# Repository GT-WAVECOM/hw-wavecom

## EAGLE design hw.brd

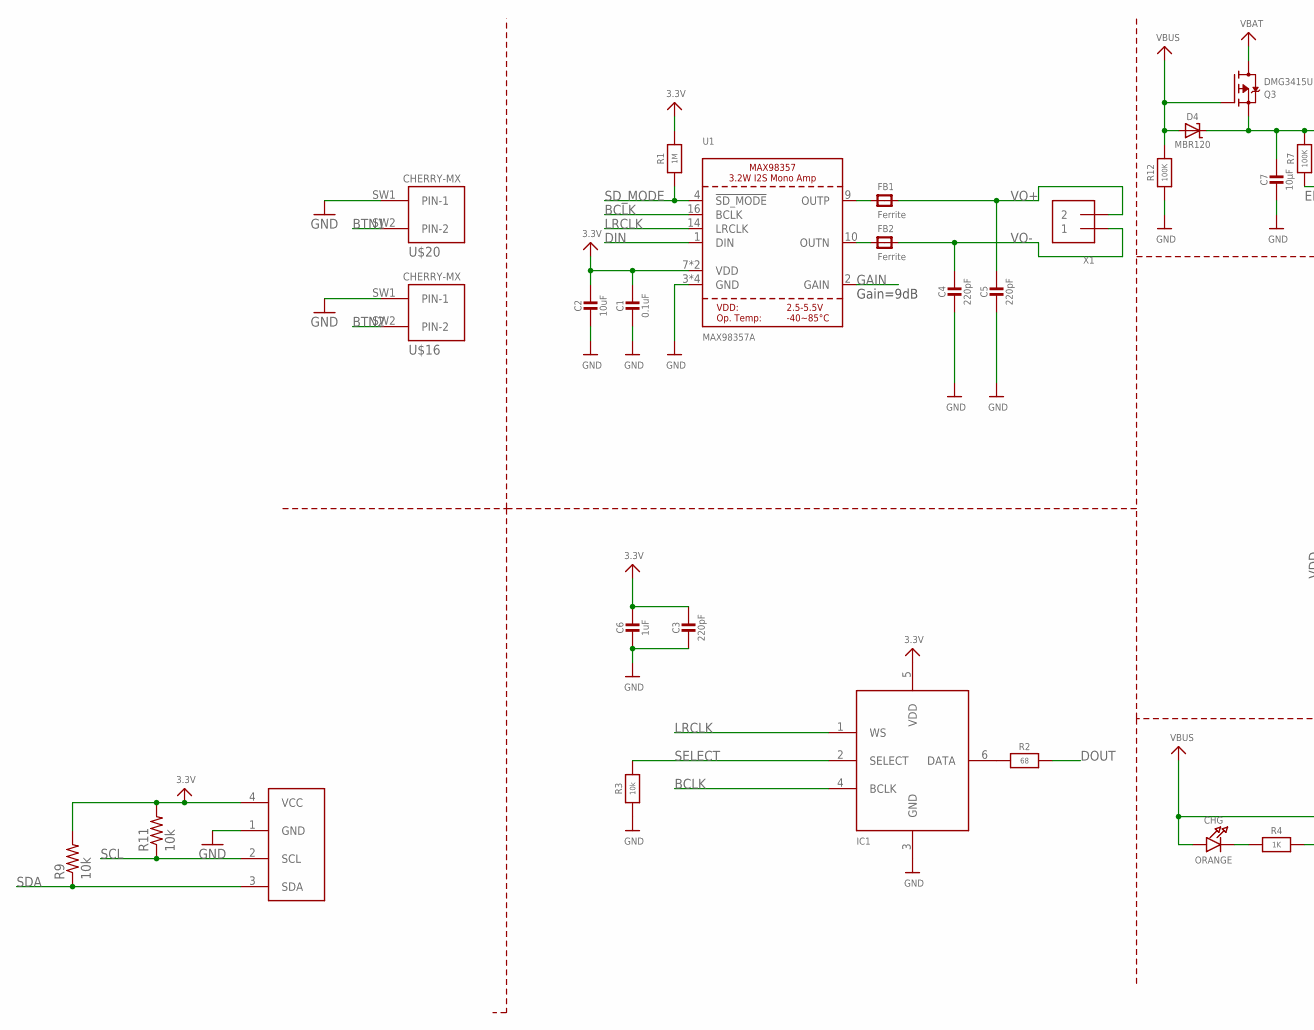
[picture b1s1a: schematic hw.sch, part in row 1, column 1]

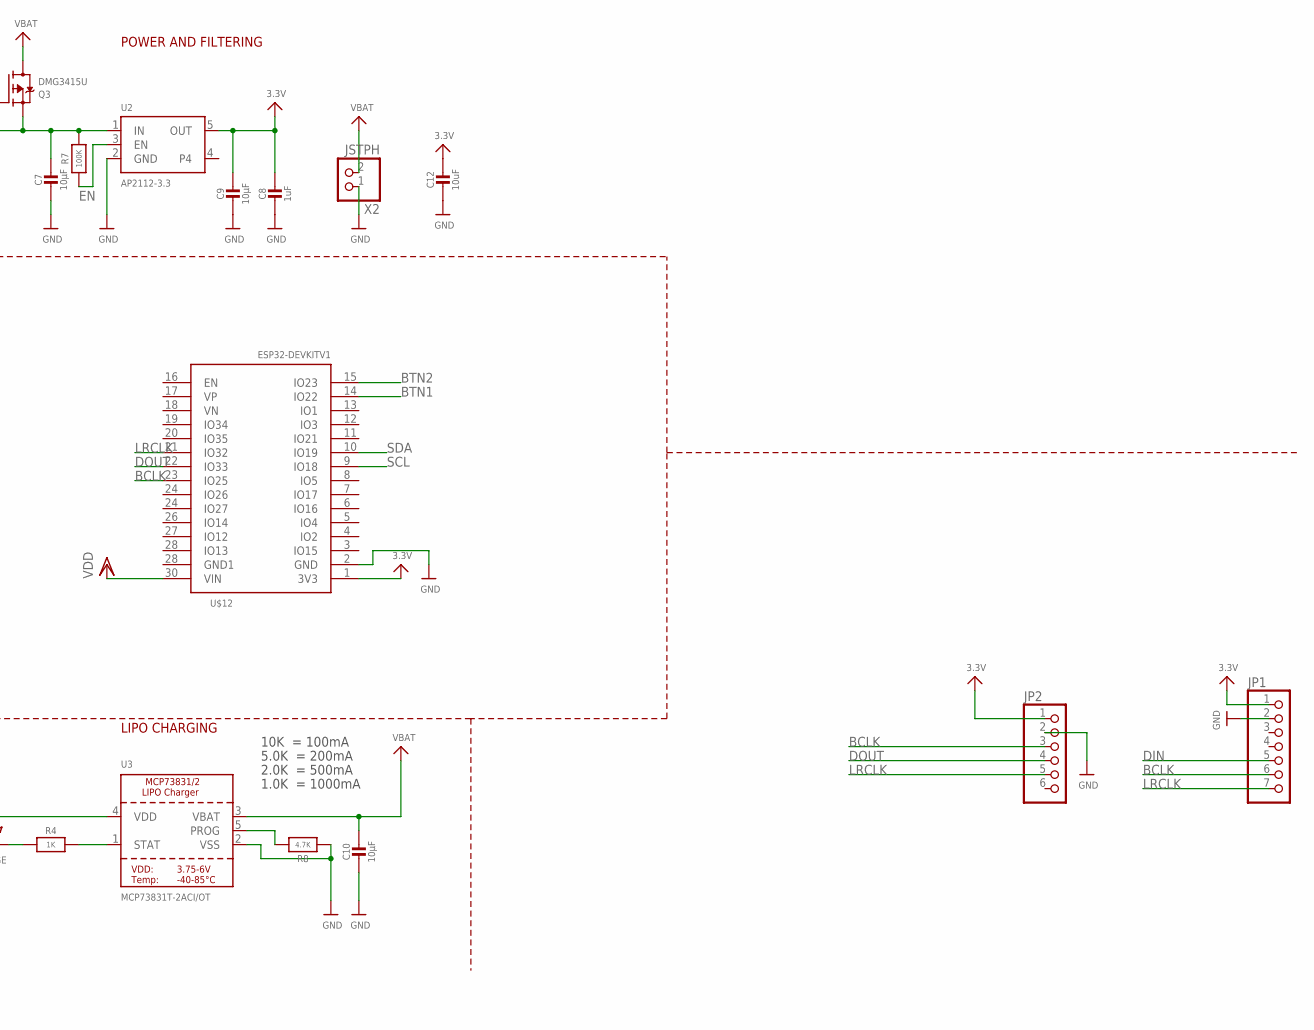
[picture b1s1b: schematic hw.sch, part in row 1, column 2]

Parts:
C1: 0.1uF; 0805-NO
C2, C12: 10uF; 0805-NO
C3, C4, C5: 220pF; 0805-NO
C6: 1uF; 0805-NO
C7, C9, C10: 10µF; 0805-NO
C8: 1uF; 0603-NO
CHG: ORANGE; CHIPLED_0805_NOOUTLINE
D4: MBR120; SOD-123
FB1, FB2: Ferrite; 0805-NO
IC1: MIC_I2S_SPH0645; SPH0645LM4H
JP1: HEADER-1X7THICKER; 1X07_ROUND_76
JP2: HEADER-1X6ROUND; 1X06_ROUND
Q3: DMG3415U; SOT23-R
R1: 1M; 0805-NO
R2: 68; 0603-NO
R3: 10k; 0603-NO
R4: 1K; 0603-NO
R7, R12: 100K; 0603-NO
R8: 4.7K; 0603-NO
R9, R11: 10k; R0805
U1: MAX98357A; QFN16_3MM
U2: AP2112-3.3; SOT23-5
U3: MCP73831T-2ACI/OT; SOT23-5
U$1: I2C_OLED; I2C_OLED_PACKAGE
U$12: ESP32DEVKITV1; ESP32-DEVKITV1
U$16, U$20: CHERRY-MX
X1: TERMBLOCK_1X2; TERMBLOCK_1X2-3.5MM
X2: JSTPH; JSTPH2

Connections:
3.3V: C1.1, C2.1, C3.1, C6.1, C8.1, C9.1, C12.1, IC1.5 (VDD), JP1.1, JP2.1, R1.2, R9.2, R11.2, U1.7 (VDD), U1.8 (VDD), U2.5 (OUT), U$1.4 (VCC), U$12.1 (3V3)
BCLK: IC1.4 (BCLK), JP1.6, JP2.3, U1.16 (BCLK), U$12.23 (IO25)
BTN1: U$12.14 (IO22), U$20.SW2 (PIN-2)
BTN2: U$12.15 (IO23), U$16.SW2 (PIN-2)
DIN: JP1.5, U1.1 (DIN)
DOUT: JP2.4, R2.2, U$12.22 (IO33)
EN: R7.1, U2.3 (EN)
GAIN: U1.2 (GAIN)
GND: C1.2, C2.2, C3.2, C4.2, C5.2, C6.2, C7.2, C8.2, C9.2, C10.2, C12.2, IC1.3 (GND), JP1.2, JP2.2, R3.1, R8.1, R12.1, U1.3 (GND), U1.11 (GND), U1.15 (GND), U1.THERMAL (GND), U2.2 (GND), U3.2 (VSS), U$1.1 (GND), U$12.2 (GND), U$16.SW1 (PIN-1), U$20.SW1 (PIN-1), X2.1
LRCLK: IC1.1 (WS), JP1.7, JP2.5, U1.14 (LRCLK), U$12.21 (IO32)
unnamed: IC1.6 (DATA), R2.1
unnamed: CHG.C, R4.1
unnamed: R4.2, U3.1 (STAT)
unnamed: R8.2, U3.5 (PROG)
unnamed: FB2.1, U1.10 (OUTN)
unnamed: FB1.1, U1.9 (OUTP)
unnamed: C7.1, D4.C, Q3.2 (S), R7.2, U2.1 (IN)
SCL: R11.1, U$1.2 (SCL), U$12.9 (IO18)
SDA: R9.1, U$1.3 (SDA), U$12.10 (IO19)
SD_MODE: R1.1, U1.4 (!SD_MODE)
SELECT: IC1.2 (SELECT), R3.2
VBAT: C10.1, Q3.3 (D), U3.3 (VBAT), X2.2
VBUS: CHG.A, D4.A, Q3.1 (G), R12.2, U3.4 (VDD)
VDD: U$12.30 (VIN)
VO+: C5.1, FB1.2, X1.2
VO-: C4.1, FB2.2, X1.1

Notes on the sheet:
Gain=9dB
POWER AND FILTERING
10K = 100mA
5.0K = 200mA
2.0K = 500mA
1.0K = 1000mA
LIPO CHARGING

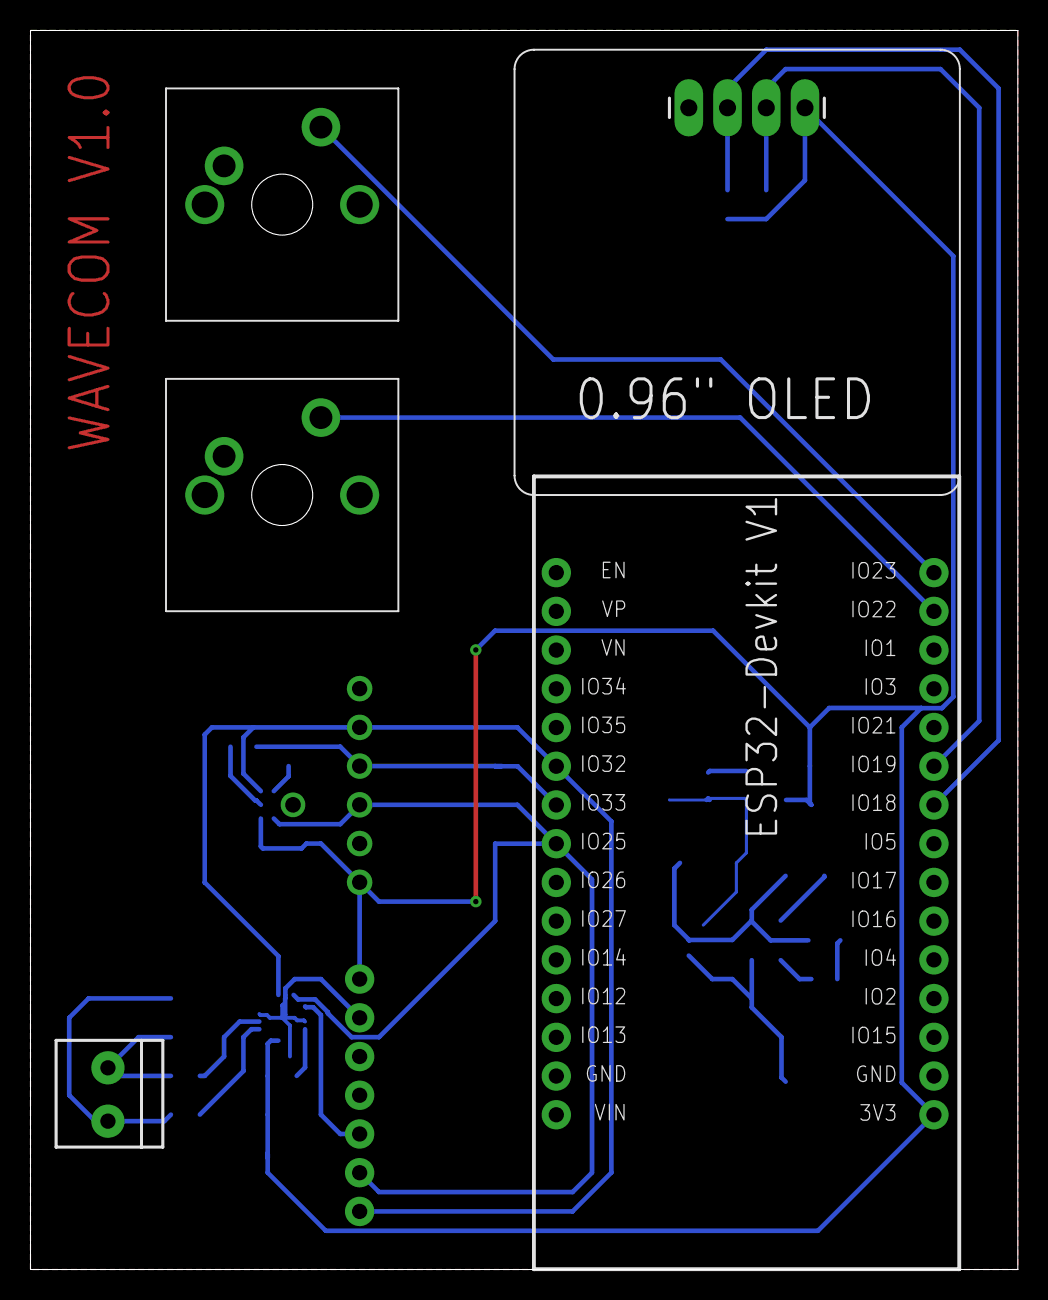
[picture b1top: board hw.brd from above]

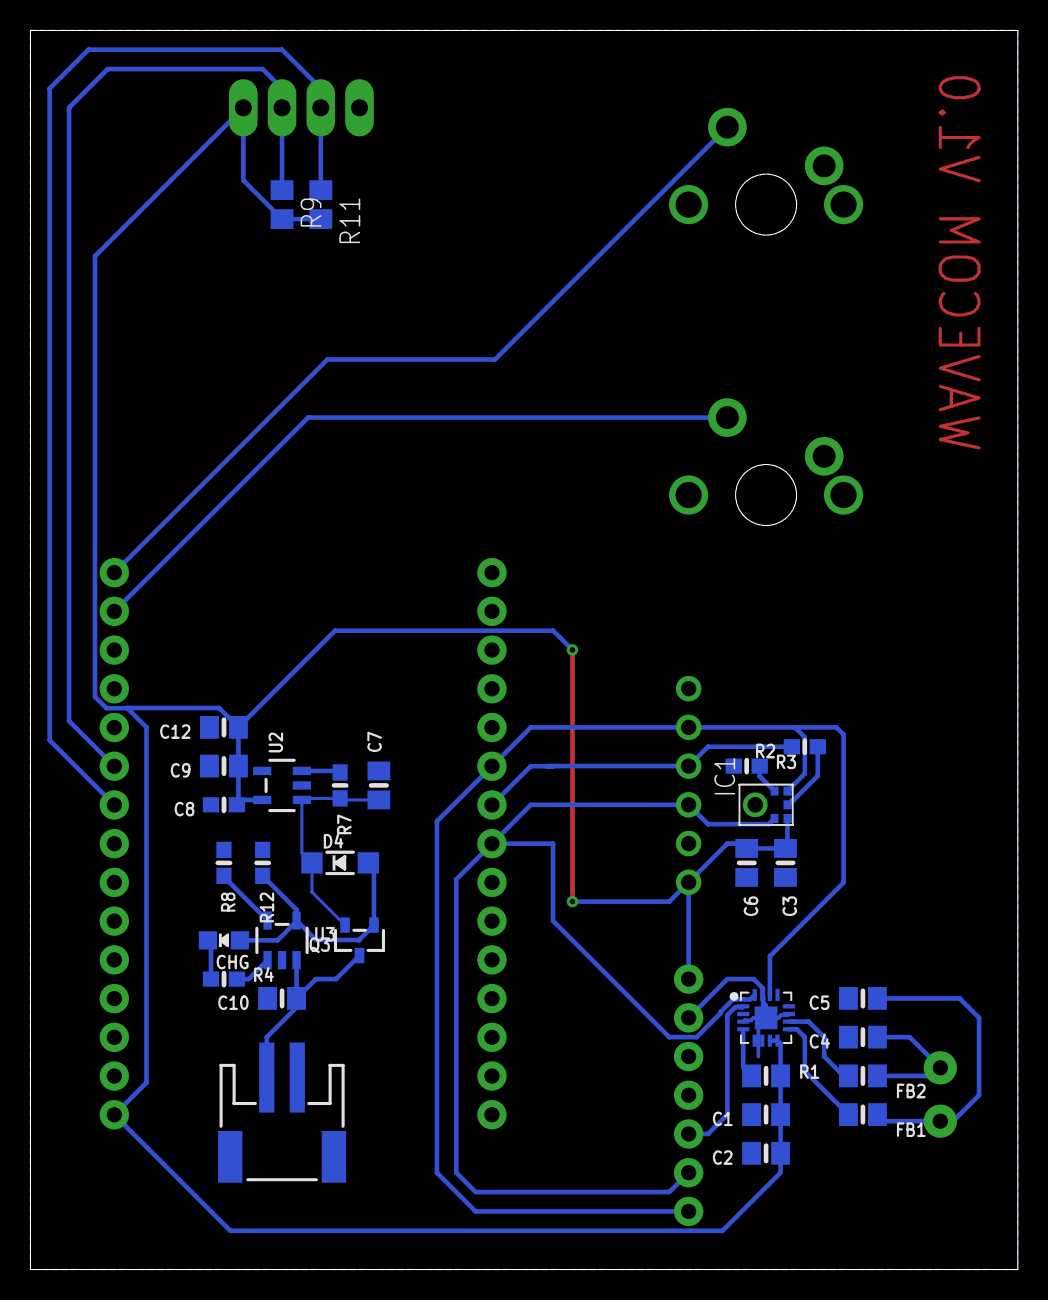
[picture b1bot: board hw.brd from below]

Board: 2 copper layers, 64.8 x 81.3 mm, 37 parts (30 on the bottom side), 24 nets.

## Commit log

2019-10-30 getting started on schematic
2019-10-30 using assembled esp32 devkitv1
2019-10-30 routing
2019-10-30 more routing
2019-11-01 rerouting :|
2019-11-01 it works out!
2019-11-01 reducing pcb size
2019-11-01 touch ups before ground plane
2019-11-01 some more adjustements for better coverage
2019-11-01 ground plane!
2019-11-01 changing cherrymx part to avoid large etch-off area
2019-11-01 some cleanup
2019-11-07 flipping esp32 around
2019-11-07 ground planes
2019-11-07 filling planes

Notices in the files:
parts and their libraries:
microbuilder: This work is placed in the public domain, and may be freely used for commercial and non-commercial work with the following conditions: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
